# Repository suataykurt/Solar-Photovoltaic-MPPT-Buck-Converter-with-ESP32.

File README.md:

# Solar Photovoltaic MPPT Buck Converter with ESP32

An end-to-end power electronics engineering project featuring a custom PCB, embedded firmware, and Simulink verification. This system extracts the maximum available power from a solar photovoltaic (PV) panel using a Buck (step-down) converter architecture driven by the Perturb and Observe (P&O) algorithm.

## 📋 Project Overview
Solar panels have non-linear voltage-current (V-I) characteristics heavily dependent on irradiance and temperature. Directly connecting a load to a PV panel results in severe power mismatch. This project solves that inefficiency by implementing an active DC-DC Buck converter. Controlled by an ESP32-WROOM-32 module, the system constantly monitors panel voltage and current, dynamically adjusting the high-side MOSFET's PWM duty cycle to lock the panel at its Maximum Power Point (MPP).

## 🛠 Technical Architecture
The project is built across three core engineering disciplines:

### 1. Mathematical Simulation (MATLAB/Simulink)
- Modeled a 213W PV array connected to an ideal Buck converter topology.
- Implemented and verified the P&O algorithm to ensure stable duty cycle convergence.
- Achieved ~96.5% tracking efficiency, extracting a stable 205W at the 29V MPP.

### 2. Embedded Firmware (ESP32 C/C++)
- **Sensors:** Reads PV voltage via a resistor divider and current via an ACS712 Hall-effect sensor module, utilizing a 16-sample moving average software filter.
- **Hardware PWM:** Uses the ESP32 LEDC peripheral to generate a clean, non-blocking 20 kHz, 10-bit PWM signal.
- **MPPT Loop:** Executes the P&O algorithm every 5 milliseconds to continuously optimize the duty cycle.
- **Telemetry:** Streams live $V_{pv}$, $I_{pv}$, $P_{pv}$, and Duty Cycle data to the Serial Plotter every 50ms, acting as a virtual oscilloscope.

### 3. Hardware & PCB Design (KiCad 7)
- **Power Stage:** IRFZ44N N-Channel Power MOSFET, MBR20100CT Schottky freewheeling diode, and a 1mH Toroidal Inductor.
- **Gate Drive:** IR2104 High-Side MOSFET driver with a bootstrap circuit (1N4148 and 1uF capacitor).
- **PCB Layout:** A 2-layer board layout optimized for power electronics, featuring widened high-current traces, proper component keep-out zones for the ESP32 antenna, and a continuous bottom copper ground plane (B.Cu) for noise reduction and EMI mitigation.

## 🚀 Key Features
- **Perturb and Observe (P&O):** A robust algorithm that continually seeks the peak of the PV power curve.
- **High-Frequency Switching:** Operates at 20 kHz to minimize inductor size and output voltage ripple.
- **Open-Circuit Protection:** Automatically cuts PWM output if panel voltage drops below 12V.
- **Production Ready:** Includes fully DRC-cleared Gerber files and a Bill of Materials (BOM) ready for fabrication (JLCPCB/PCBWay).

## 📂 Project Structure
To maintain an organized repository, the files have been structured as follows:

- `Simulink/`
  - `mppt_buck_model.slx`: The main Simulink model file.
  - `matlab_code.m`: MATLAB initialization script for workspace variables.
  - `matlab_sim.jpg`: Screenshot of the simulation results.
- `Firmware/`
  - `esp_code.ino`: The main embedded C++ source code for the ESP32.
- `Hardware/`
  - `mppt_buck_model.kicad_sch`: KiCad schematic file.
  - `mppt_buck_model.kicad_pcb`: KiCad PCB layout file.
  - `mppt_buck_model.kicad_pro`: KiCad project file.
  - `mppt_buck_model.csv`: Bill of Materials (BOM) for component sourcing.
  - `Images/`: Contains 3D renders of the PCB (`mppt_buck_model.png`, `mppt_buck_model_backside.png`).
- `Hardware/Gerber_Outputs/`
  - Directory containing all `.gbr` (Copper, Mask, Paste, Silkscreen, Edge Cuts) and `.drl` files required for PCB manufacturing.

## 💡 How to Use
1. **Simulation:** Open `matlab_code.m` in MATLAB to load workspace parameters, then run `mppt_buck_model.slx` to observe the theoretical MPPT tracking.
2. **Firmware:** Open `esp_code.ino` using the Arduino IDE (with ESP32 board manager installed) or PlatformIO. Compile and flash it to your ESP32 module.
3. **Hardware Fabrication:** Zip the contents of the `Hardware/Gerber_Outputs/` directory and upload it to a PCB manufacturer. Use the `mppt_buck_model.csv` BOM file to order components.

---
*Developed by Suat Aykurt*

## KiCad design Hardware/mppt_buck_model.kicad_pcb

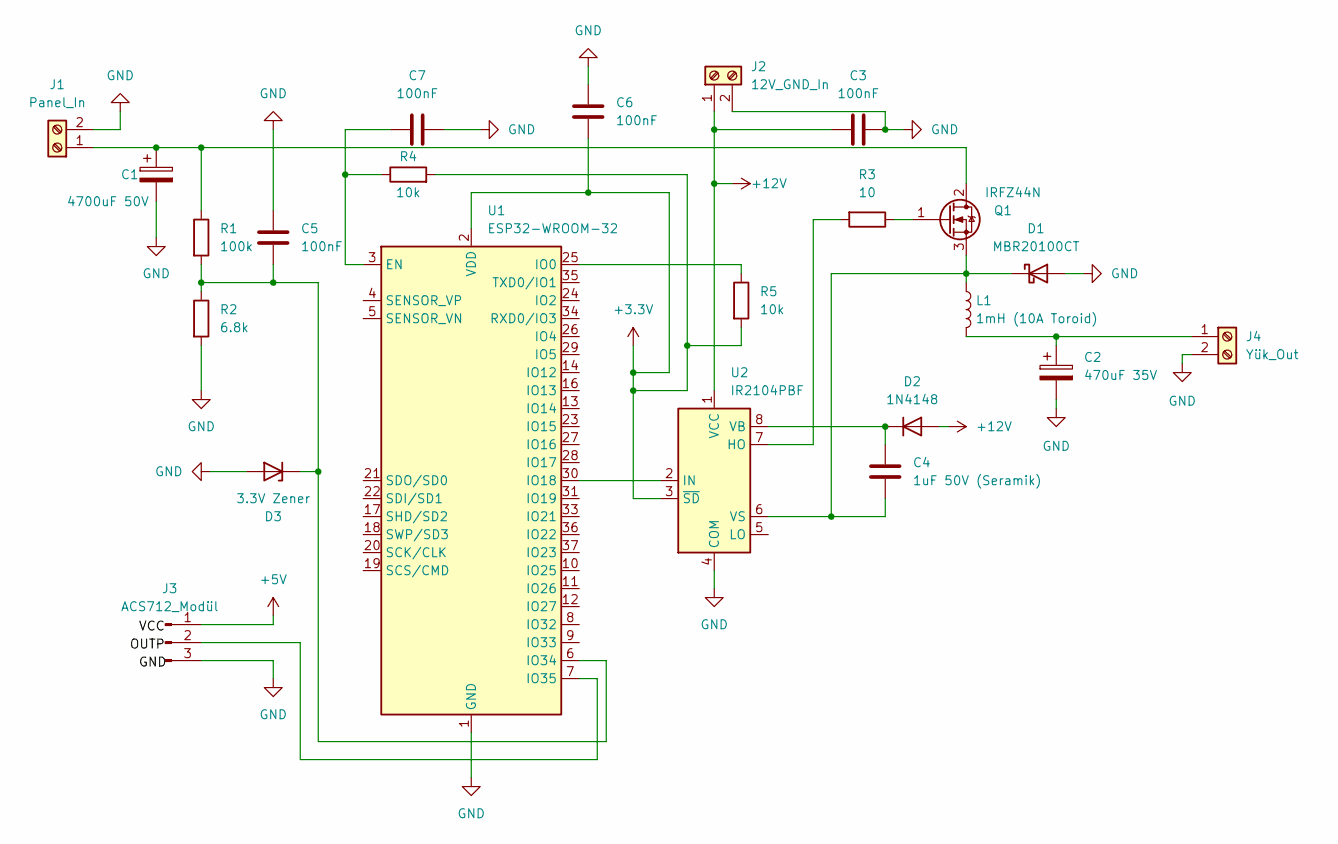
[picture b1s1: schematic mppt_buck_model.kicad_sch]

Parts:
C1: 4700uF 50V; CP_Radial_D16.0mm_P7.50mm
C2: 470uF 35V; CP_Radial_D10.0mm_P5.00mm
C3, C5, C6, C7: 100nF; C_Disc_D5.0mm_W2.5mm_P5.00mm
C4: 1uF 50V (Seramik); C_Disc_D5.0mm_W2.5mm_P5.00mm
D1: MBR20100CT; TO-220-2_Vertical
D2: 1N4148; D_DO-35_SOD27_P7.62mm_Horizontal
D3: 3.3V Zener; D_DO-35_SOD27_P7.62mm_Horizontal
J1: Panel_In; TerminalBlock_Phoenix_MKDS-1,5-2-5.08_1x02_P5.08mm_Horizont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
J2: 12V_GND_In; TerminalBlock_Phoenix_MKDS-1,5-2-5.08_1x02_P5.08mm_Horizont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
J3: ACS712_Modül; PinHeader_1x03_P2.54mm_Vertical
J4: Yük_Out; TerminalBlock_Phoenix_MKDS-1,5-2-5.08_1x02_P5.08mm_Horizont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
L1: 1mH (10A Toroid); L_Toroid_Vertical_L21.6mm_W11.4mm_P7.62mm_Pulse_KM-3
Q1: IRFZ44N; TO-220-3_Vertical
R1: 100k; R_Axial_DIN0207_L6.3mm_D2.5mm_P10.16mm_Horizontal
R2: 6.8k; R_Axial_DIN0207_L6.3mm_D2.5mm_P10.16mm_Horizontal
R3: 10; R_Axial_DIN0207_L6.3mm_D2.5mm_P10.16mm_Horizontal
R4, R5: 10k; R_Axial_DIN0207_L6.3mm_D2.5mm_P10.16mm_Horizontal
U1: ESP32-WROOM-32
U2: IR2104PBF; DIP-8_W7.62mm

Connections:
+3.3V: C6.1, R4.2, R5.2, U1.2 (VDD), U2.3 (~SD)
+5V: J3.1
+12V: C3.1, D2.2 (A), J2.1, U2.1 (VCC)
GND: C1.2, C2.2, C3.2, C5.2, C6.2, C7.2, D1.2 (A), D3.2 (A), J1.2, J2.2, J3.3, J4.2, R2.2, U1.1 (GND), U1.15 (GND), U1.38 (GND), U1.39 (GND), U2.4 (COM)
unnamed: C4.2, D1.1 (K), L1.1, Q1.3 (S), U2.6 (VS)
unnamed: C4.1, D2.1 (K), U2.8 (VB)
unnamed: C5.1, D3.1 (K), R1.2, R2.1, U1.6 (IO34)
unnamed: C1.1, J1.1, Q1.2 (D), R1.1
unnamed: J3.2, U1.7 (IO35)
unnamed: C2.1, J4.1, L1.2
unnamed: Q1.1 (G), R3.1
unnamed: C7.1, R4.1, U1.3 (EN)
unnamed: R5.1, U1.25 (IO0)
unnamed: U1.30 (IO18), U2.2 (IN)
unnamed: R3.2, U2.7 (HO)

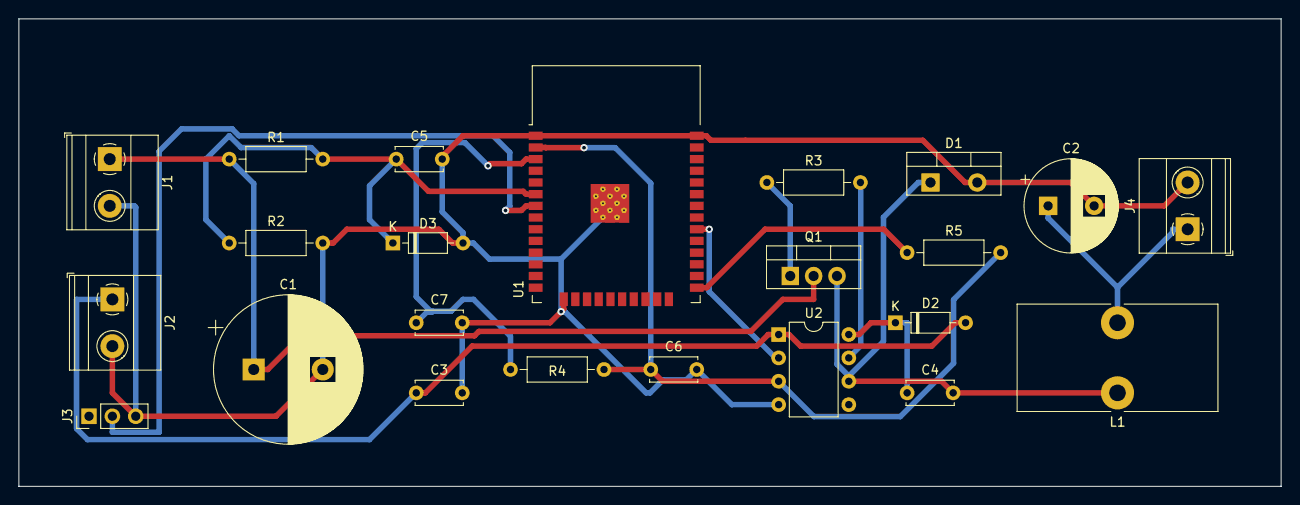
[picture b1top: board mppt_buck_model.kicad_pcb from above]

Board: 2 copper layers, 137.2 x 50.8 mm, 23 parts (0 on the bottom side), 14 nets.
